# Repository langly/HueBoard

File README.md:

# HueBoard
Some project files for my HueBoard

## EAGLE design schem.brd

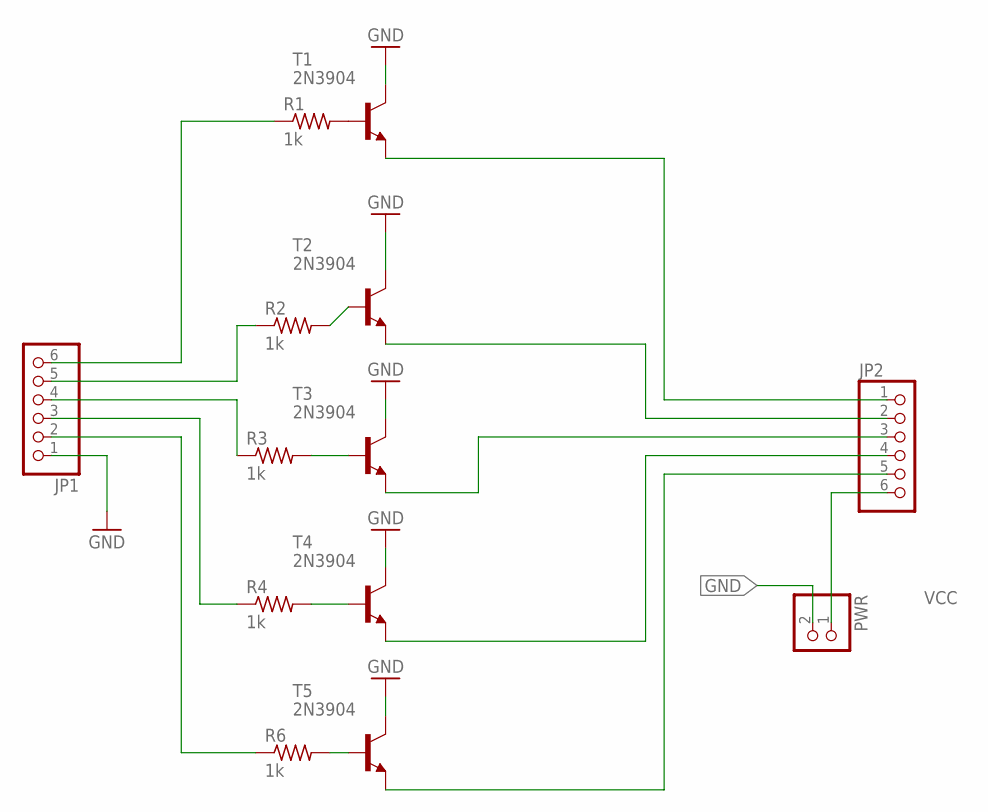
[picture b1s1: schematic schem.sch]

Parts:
JP1, JP2: PINHD-1X6; 1X06
PWR: PINHD-1X2; 1X02
R1, R2, R3, R4, R6: 1k; 0207/5V
T1, T2, T3, T4, T5: 2N3904; TO92

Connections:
GND: JP1.1, PWR.2, T1.1 (C), T2.1 (C), T3.1 (C), T4.1 (C), T5.1 (C)
unnamed: JP1.6, R1.1
unnamed: R1.2, T1.2 (B)
unnamed: JP1.2, R6.1
unnamed: R3.2, T3.2 (B)
unnamed: JP1.5, R2.1
unnamed: R2.2, T2.2 (B)
unnamed: JP2.1, T1.3 (E)
unnamed: JP1.4, R3.1
unnamed: JP1.3, R4.1
unnamed: R4.2, T4.2 (B)
unnamed: JP2.2, T2.3 (E)
unnamed: R6.2, T5.2 (B)
unnamed: JP2.3, T3.3 (E)
unnamed: JP2.4, T4.3 (E)
unnamed: JP2.5, T5.3 (E)
VCC: JP2.6, PWR.1

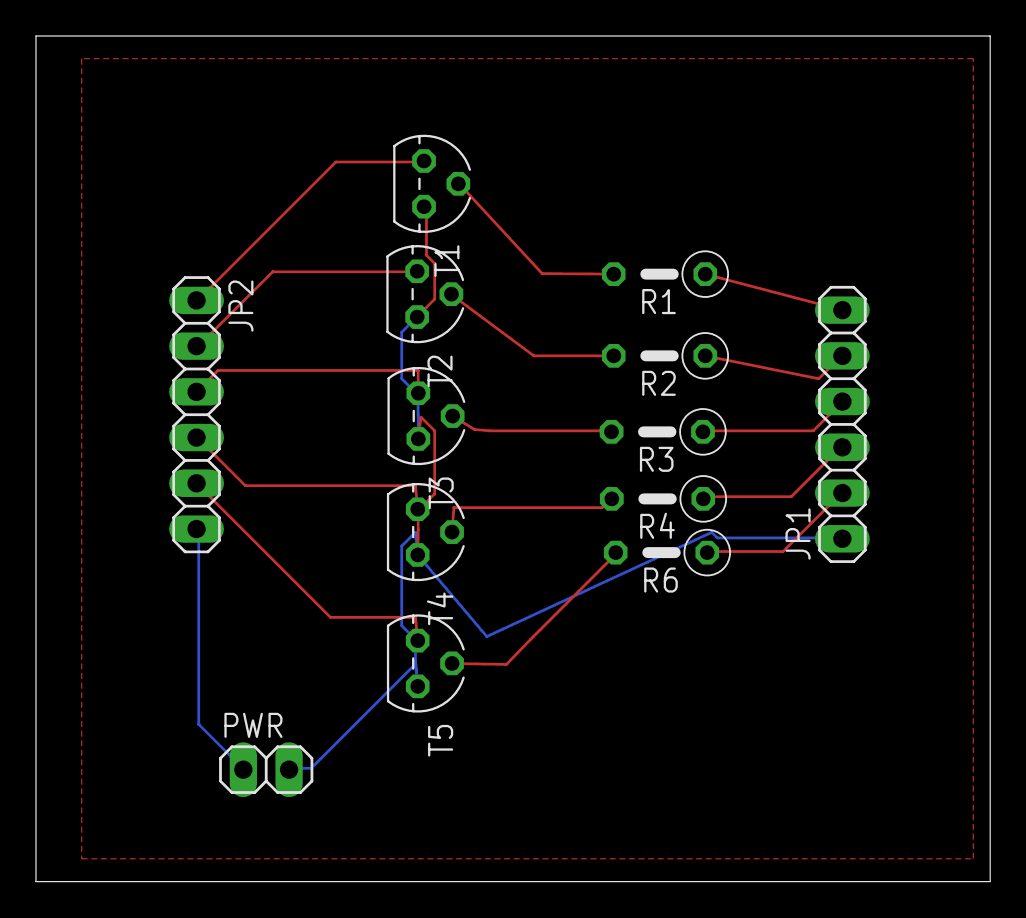
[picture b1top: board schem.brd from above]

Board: 2 copper layers, 53.0 x 47.0 mm, 13 parts (0 on the bottom side), 17 nets.

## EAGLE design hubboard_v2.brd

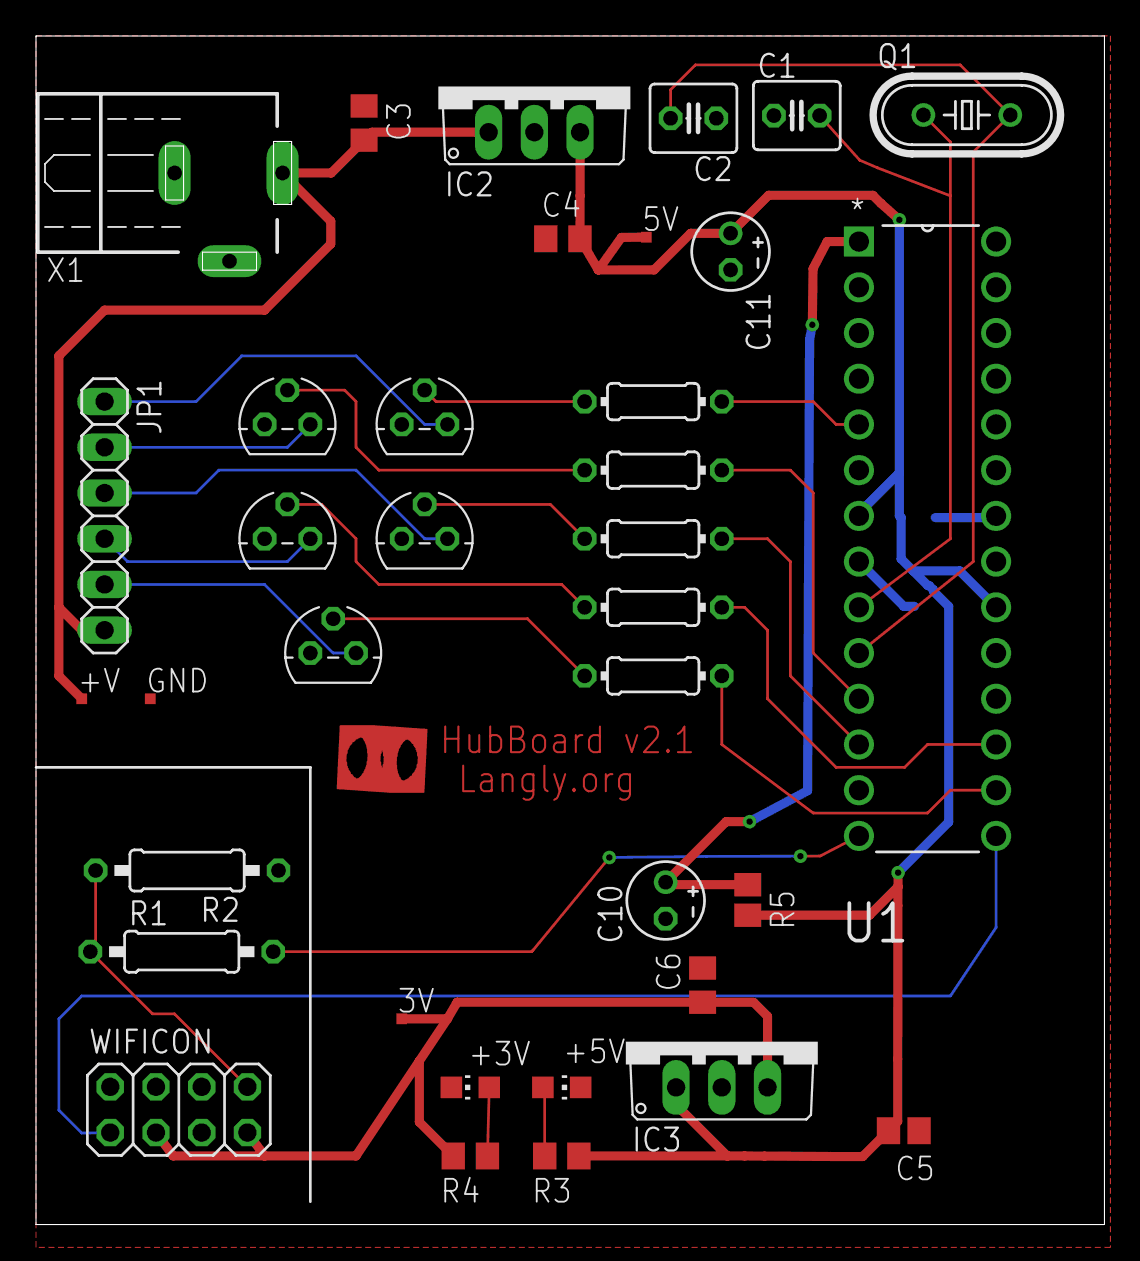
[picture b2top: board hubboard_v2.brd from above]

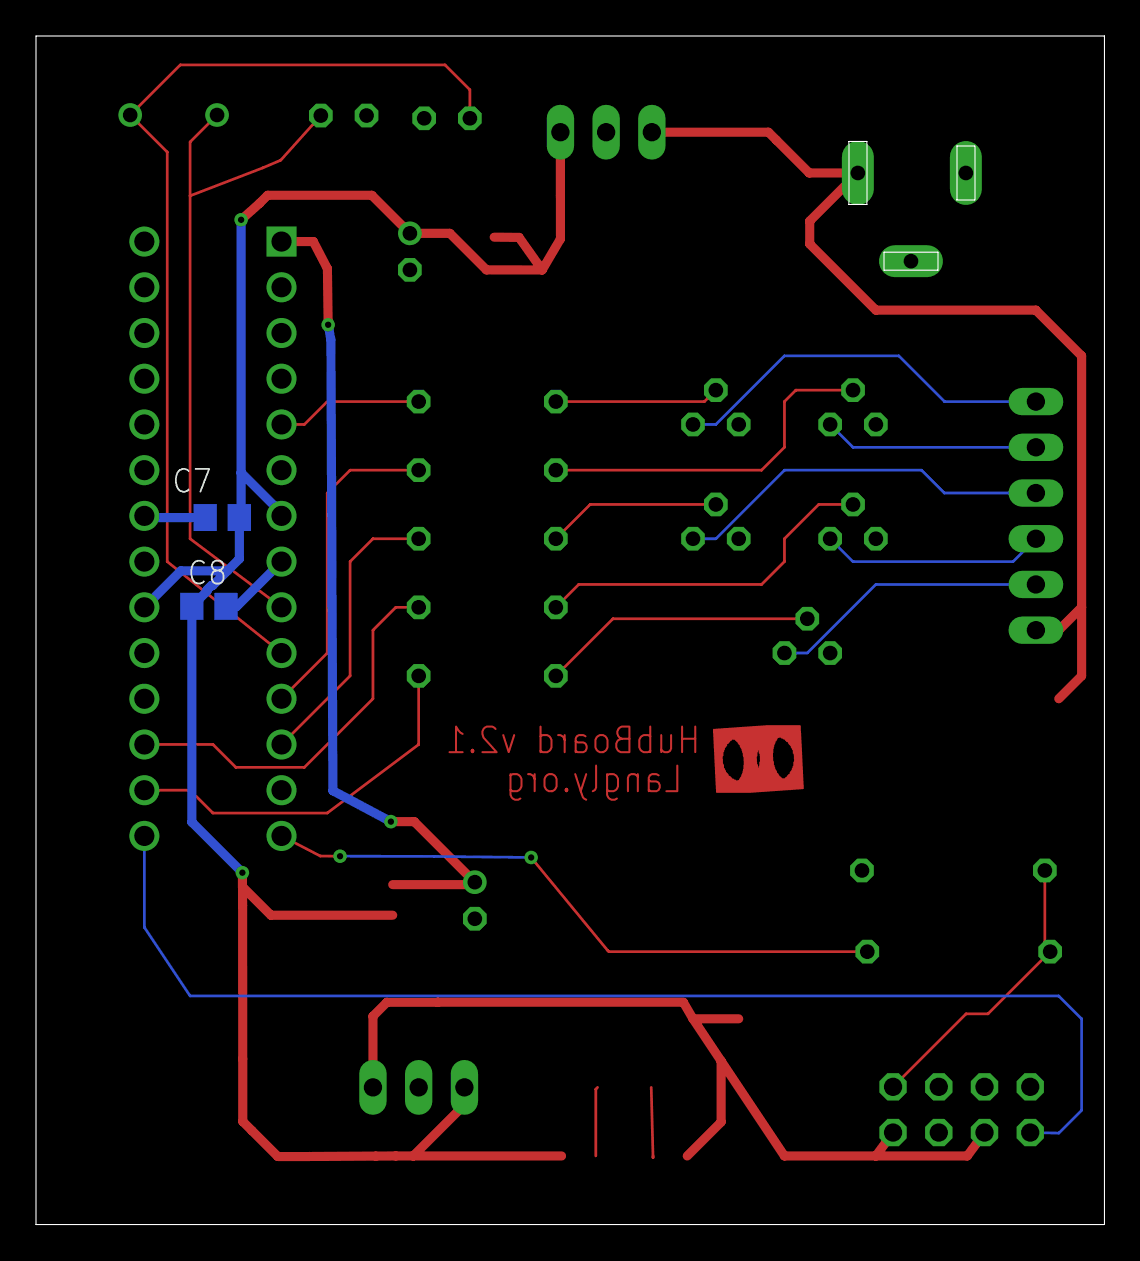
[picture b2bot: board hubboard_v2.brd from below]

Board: 2 copper layers, 59.4 x 66.0 mm, 38 parts (2 on the bottom side), 27 nets.

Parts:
3V, 5V: TPTP06SQ; TP06SQ
+3V: Vf-3.3; CHIP-LED0805
+5V: Vf-2.1; CHIP-LED0805
+V: TPTP06SQ; TP06SQ
C1, C2: 20uf; C025-040X050
C3: 0.33uf; C0805
C4, C6, C7, C8: 0.1uf; C0805
C5: 0.33uf; C2012
C10, C11: 10uf; E2-4
GND: TPTP06SQ; TP06SQ
IC2, IC3: 788TV; TO220V
JP1: 1X06
LED_CTRL1:Q1, LED_CTRL2:Q1, LED_CTRL3:Q1, LED_CTRL4:Q1, LED_CTRL5:Q1: 2N3904; TO92
LED_CTRL1:R1, LED_CTRL2:R1, LED_CTRL3:R1, LED_CTRL4:R1, LED_CTRL5:R1: 1k; 0204/7
Q1: 16mhz; HC49/S
R1: 1k; 0207/10
R2: 2.2k; 0207/10
R3: 170; R0805
R4: 0; R0805
R5: 1k; R2012
U1: ATMEGA328P-PU; DIP254P762X457-28
WIFICON: 2X04
X1: NEB21R

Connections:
+3V.3: 3V.TP, C6.2, IC3.3, R4.2, WIFICON.3, WIFICON.7
+5V: 5V.TP, C4.2, C5.2, C7.1, C8.1, C11.+, IC2.3, IC3.1, R3.1, R5.2, U1.7, U1.20
AT_RX: U1.15, WIFICON.1
AT_TX: R1.2, U1.14
GND: +3V.C, +5V.C, C1.1, C2.1, C3.1, C4.1, C5.1, C6.1, C7.2, C8.2, C10.-, C11.-, GND.TP, IC2.2, IC3.2, LED_CTRL1:Q1.3, LED_CTRL2:Q1.3, LED_CTRL3:Q1.3, LED_CTRL4:Q1.3, LED_CTRL5:Q1.3, R2.1, U1.8, U1.22, WIFICON.2, X1.2, X1.3
LED_CTRL1:N$1: LED_CTRL1:Q1.2, LED_CTRL1:R1.2
LED_CTRL2:N$1: LED_CTRL2:Q1.2, LED_CTRL2:R1.2
LED_CTRL3:N$1: LED_CTRL3:Q1.2, LED_CTRL3:R1.2
LED_CTRL4:N$1: LED_CTRL4:Q1.2, LED_CTRL4:R1.2
LED_CTRL5:N$1: LED_CTRL5:Q1.2, LED_CTRL5:R1.2
unnamed: JP1.1, LED_CTRL1:Q1.1
unnamed: JP1.2, LED_CTRL2:Q1.1
unnamed: JP1.3, LED_CTRL3:Q1.1
unnamed: JP1.4, LED_CTRL4:Q1.1
unnamed: JP1.5, LED_CTRL5:Q1.1
unnamed: LED_CTRL4:R1.1, U1.17
unnamed: LED_CTRL1:R1.1, U1.5
unnamed: LED_CTRL3:R1.1, U1.12
unnamed: C2.2, Q1.2, U1.10
unnamed: R1.1, R2.2, WIFICON.8
unnamed: LED_CTRL5:R1.1, U1.16
unnamed: LED_CTRL2:R1.1, U1.11
unnamed: +5V.A, R3.2
unnamed: +3V.A, R4.1
unnamed: C1.2, Q1.1, U1.9
RESET: C10.+, R5.1, U1.1
VCC: +V.TP, C3.2, IC2.1, JP1.6, X1.1

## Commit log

2018-05-21 Added Hubboard v2.1
